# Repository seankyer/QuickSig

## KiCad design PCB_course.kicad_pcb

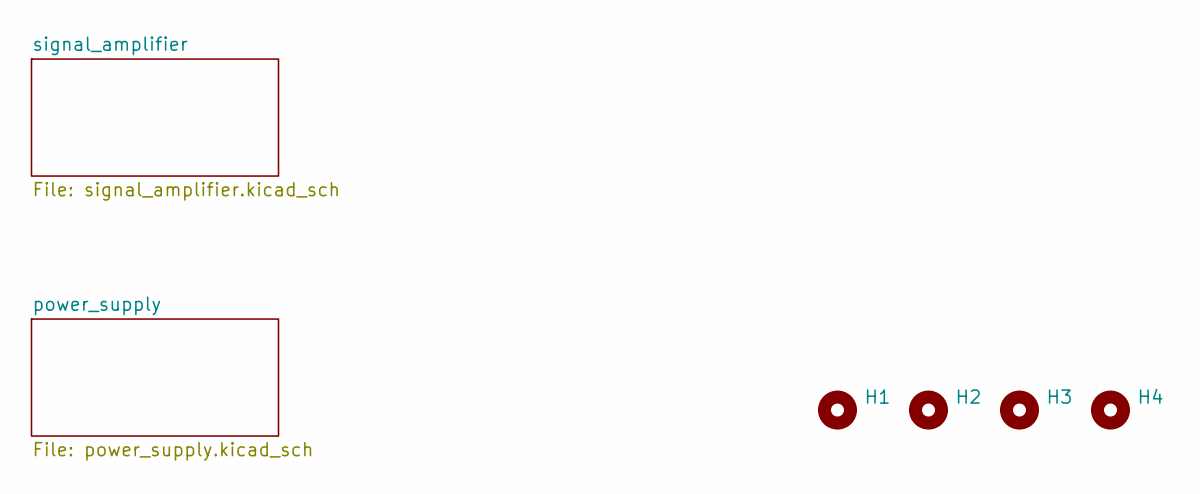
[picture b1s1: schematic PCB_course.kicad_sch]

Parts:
H1, H2, H3, H4: MountingHole_2.5mm

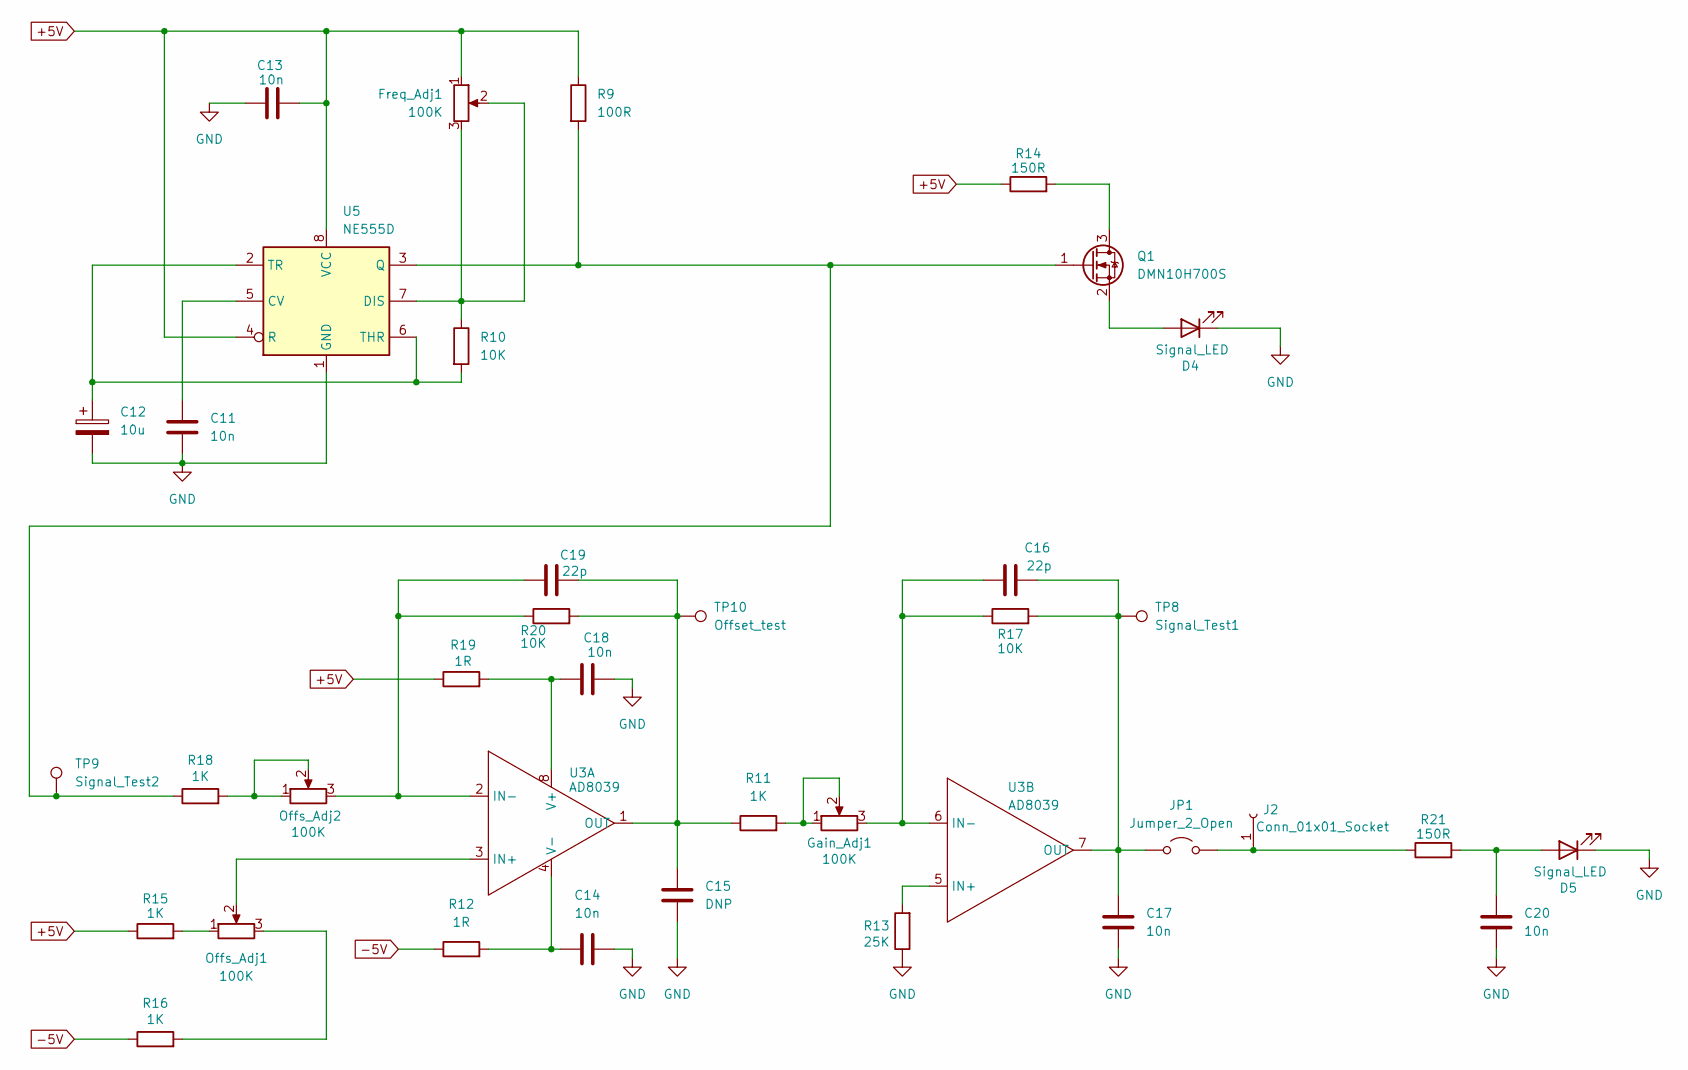
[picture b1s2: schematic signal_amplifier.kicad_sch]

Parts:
C11, C13, C14, C17, C18, C20: 10n; C_0805_2012Metric_Pad1.18x1.45mm_HandSolder
C12: 10u; CP_EIA-6032-28_Kemet-C_Pad2.25x2.35mm_HandSolder
C15: DNP; C_0805_2012Metric_Pad1.18x1.45mm_HandSolder
C16, C19: 22p; C_0805_2012Metric_Pad1.18x1.45mm_HandSolder
D4, D5: Signal_LED; D_0805_2012Metric_Pad1.15x1.40mm_HandSolder
Freq_Adj1: 100K; POT_PV36W_BRN
Gain_Adj1: 100K; POT_PV36W_BRN
J2: Conn_01x01_Socket; PinHeader_1x01_P1.00mm_Vertical
JP1: Jumper_2_Open; SolderJumper-2_P1.3mm_Open_Pad1.0x1.5mm
Offs_Adj1, Offs_Adj2: 100K; POT_PV36W_BRN
Q1: DMN10H700S; SOT-23
R9: 100R; R_0805_2012Metric_Pad1.20x1.40mm_HandSolder
R10, R17, R20: 10K; R_0805_2012Metric_Pad1.20x1.40mm_HandSolder
R11, R15, R16, R18: 1K; R_0805_2012Metric_Pad1.20x1.40mm_HandSolder
R12, R19: 1R; R_0805_2012Metric_Pad1.20x1.40mm_HandSolder
R13: 25K; R_0805_2012Metric_Pad1.20x1.40mm_HandSolder
R14, R21: 150R; R_0805_2012Metric_Pad1.20x1.40mm_HandSolder
TP8: Signal_Test1; TestPoint_Keystone_5000-5004_Miniature
TP9: Signal_Test2; TestPoint_Keystone_5000-5004_Miniature
TP10: Offset_test; TestPoint_Keystone_5000-5004_Miniature
U3: AD8039; MAX889
U5: NE555D; MAX889

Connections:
+5V: C13.1, Freq_Adj1.1, R9.1, R14.1, R15.1, R19.1, U5.4 (R), U5.8 (VCC); also elsewhere on the board
-5V: R12.1, R16.1; also elsewhere on the board
GND: C11.2, C12.2, C13.2, C14.2, C15.1, C17.2, C18.2, C20.2, D4.1 (K), D5.1 (K), R13.1, U5.1 (GND); also elsewhere on the board
unnamed: D4.2 (A), Q1.2 (S)
unnamed: C20.1, D5.2 (A), R21.2
unnamed: Gain_Adj1.1, Gain_Adj1.2, R11.2
unnamed: J2.1, JP1.2 (B), R21.1
unnamed: C16.1, C17.1, JP1.1 (A), R17.2, TP8.1, U3.7 (OUT)
unnamed: Offs_Adj1.1, R15.2
unnamed: Offs_Adj1.3, R16.2
unnamed: Offs_Adj2.1, Offs_Adj2.2, R18.2
unnamed: Q1.3 (D), R14.2
unnamed: Q1.1 (G), R9.2, R18.1, TP9.1, U5.3 (Q)
unnamed: Offs_Adj1.2, U3.3 (IN+)
unnamed: C19.1, Offs_Adj2.3, R20.1, U3.2 (IN-)
unnamed: C15.2, C19.2, R11.1, R20.2, TP10.1, U3.1 (OUT)
unnamed: C18.1, R19.2, U3.8 (V+)
unnamed: C14.1, R12.2, U3.4 (V-)
unnamed: R13.2, U3.5 (IN+)
unnamed: C16.2, Gain_Adj1.3, R17.1, U3.6 (IN-)
unnamed: C11.1, U5.5 (CV)
unnamed: Freq_Adj1.2, Freq_Adj1.3, R10.1, U5.7 (DIS)
unnamed: C12.1, R10.2, U5.2 (TR), U5.6 (THR)

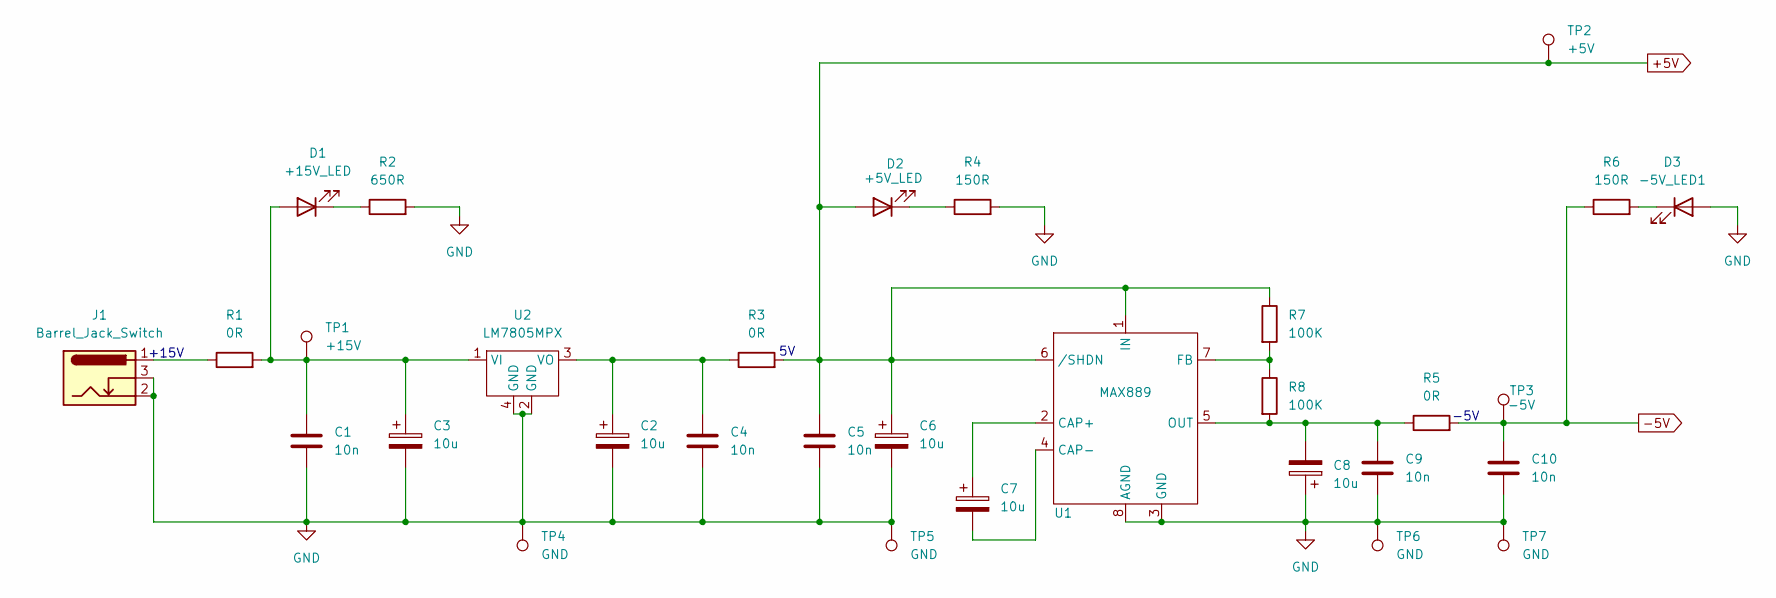
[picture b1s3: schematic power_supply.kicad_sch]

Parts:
C1, C4, C5, C9, C10: 10n; C_0805_2012Metric_Pad1.18x1.45mm_HandSolder
C2, C3, C6, C7, C8: 10u; CP_EIA-6032-28_Kemet-C_Pad2.25x2.35mm_HandSolder
D1: +15V_LED; D_0805_2012Metric_Pad1.15x1.40mm_HandSolder
D2: +5V_LED; D_0805_2012Metric_Pad1.15x1.40mm_HandSolder
D3: -5V_LED1; D_0805_2012Metric_Pad1.15x1.40mm_HandSolder
J1: Barrel_Jack_Switch; BarrelJack_Wuerth_6941xx301002
R1, R3, R5: 0R; R_0805_2012Metric_Pad1.20x1.40mm_HandSolder
R2: 650R; R_0805_2012Metric_Pad1.20x1.40mm_HandSolder
R4, R6: 150R; R_0805_2012Metric_Pad1.20x1.40mm_HandSolder
R7, R8: 100K; R_0805_2012Metric_Pad1.20x1.40mm_HandSolder
TP1: +15V; TestPoint_Keystone_5000-5004_Miniature
TP2: +5V; TestPoint_Keystone_5000-5004_Miniature
TP3: -5V; TestPoint_Keystone_5000-5004_Miniature
TP4, TP5, TP6, TP7: GND; TestPoint_Keystone_5000-5004_Miniature
U1: MAX889
U2: LM7805MPX; DCY4_TEX-M

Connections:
+5V: C5.1, C6.1, D2.2 (A), R3.2, R7.1, TP2.1, U1.1 (IN), U1.6 (/SHDN); also elsewhere on the board
-5V: C10.1, R5.2, R6.1, TP3.1; also elsewhere on the board
GND: C1.2, C2.2, C3.2, C4.2, C5.2, C6.2, C8.1, C9.2, C10.2, D3.2 (A), J1.2, J1.3, R2.2, R4.2, TP4.1, TP5.1, TP6.1, TP7.1, U1.3 (GND), U1.8 (AGND), U2.2 (GND), U2.4 (GND); also elsewhere on the board
unnamed: C1.1, C3.1, D1.2 (A), R1.2, TP1.1, U2.1 (VI)
unnamed: D1.1 (K), R2.1
unnamed: D2.1 (K), R4.1
unnamed: D3.1 (K), R6.2
unnamed: J1.1, R1.1
unnamed: C7.1, U1.2 (CAP+)
unnamed: C7.2, U1.4 (CAP-)
unnamed: R7.2, R8.1, U1.7 (FB)
unnamed: C8.2, C9.1, R5.1, R8.2, U1.5 (OUT)
unnamed: C2.1, C4.1, R3.1, U2.3 (VO)

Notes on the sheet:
-5V
+15V

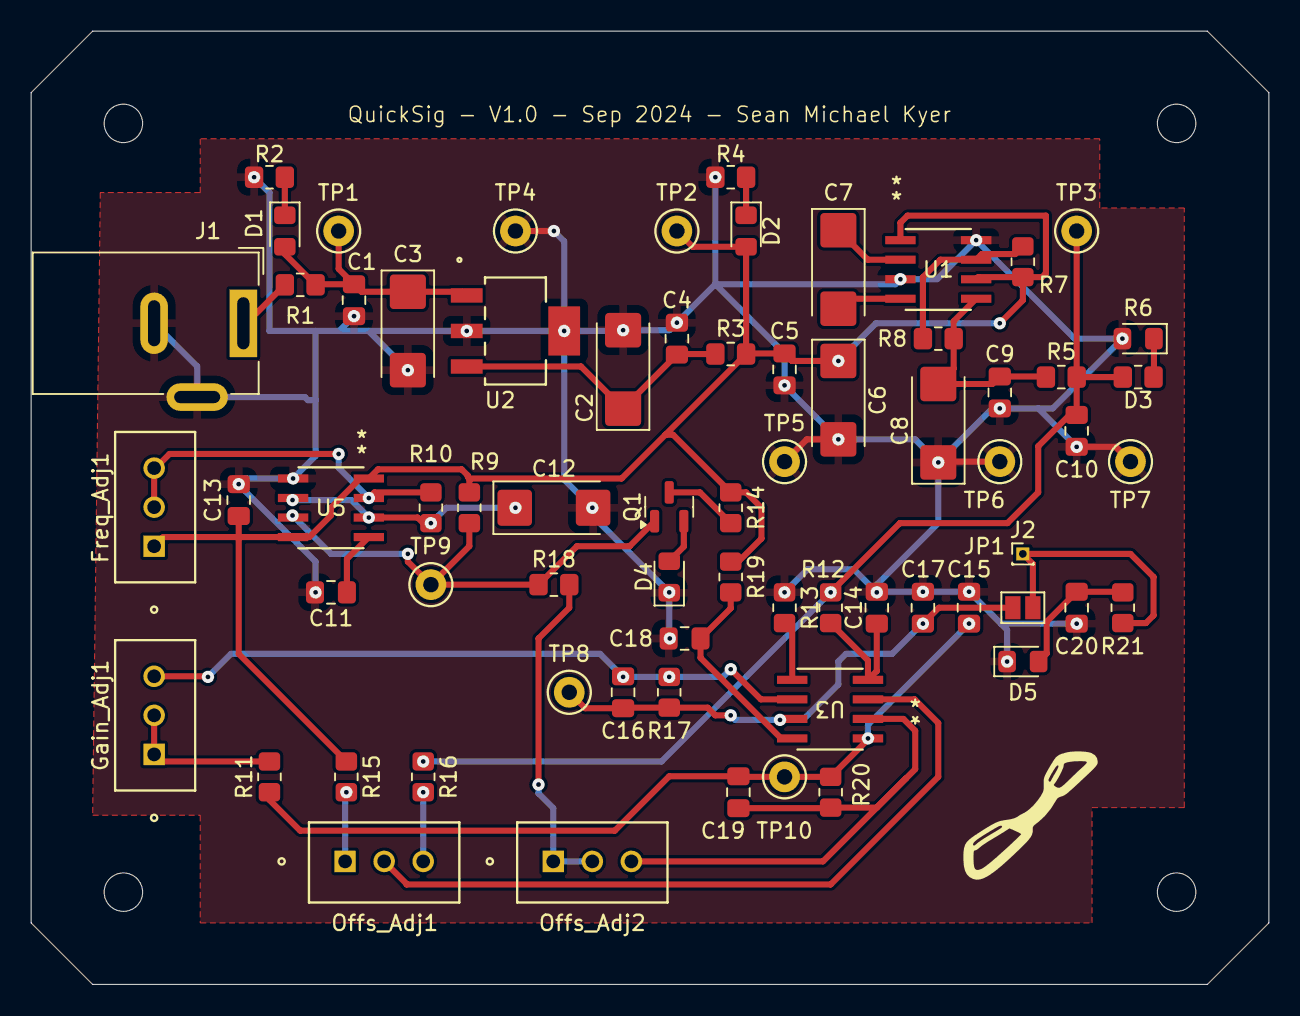
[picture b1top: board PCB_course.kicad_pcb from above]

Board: 2 copper layers, 80.5 x 62.0 mm, 72 parts (0 on the bottom side), 33 nets.

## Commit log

2024-11-17 Add KiCad files via upload
2024-11-17 Uploaded images of final PCB
